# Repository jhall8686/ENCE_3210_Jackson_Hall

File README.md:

# ENCE_3210_Jackson_Hall
Microprocessor Systems Project Submissions

---

The primary project in this repository is the **ThermoPro Thermometer Probe**, a clone of an actual product implemented on a PCB shield. All of the PCB docs and firmware can be found here.

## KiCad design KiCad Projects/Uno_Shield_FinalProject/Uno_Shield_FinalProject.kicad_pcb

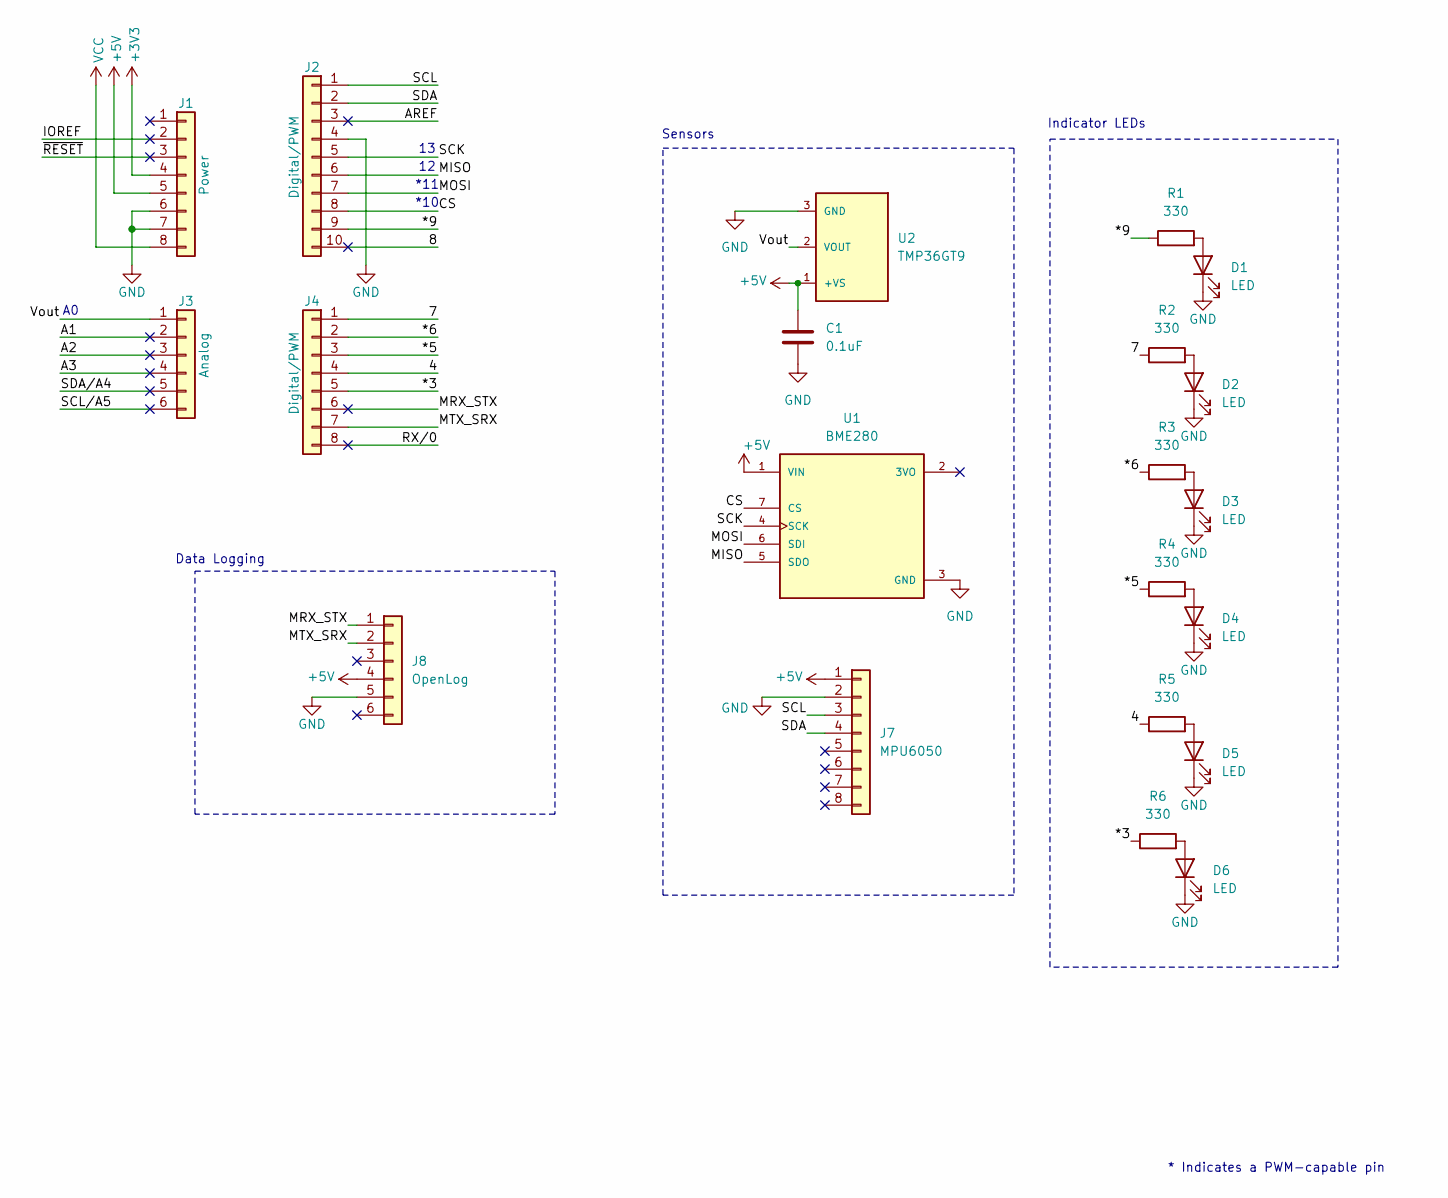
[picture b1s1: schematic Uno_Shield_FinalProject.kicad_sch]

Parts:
C1: 0.1uF; CP_Radial_D6.3mm_P2.50mm
D1, D2, D3, D4, D5, D6: LED; LED_D3.0mm
J1: Power; PinSocket_1x08_P2.54mm_Vertical
J2: Digital/PWM; PinSocket_1x10_P2.54mm_Vertical
J3: Analog; PinSocket_1x06_P2.54mm_Vertical
J4: Digital/PWM; PinSocket_1x08_P2.54mm_Vertical
J7: MPU6050; PinSocket_1x08_P2.54mm_Vertical
J8: OpenLog; MODULE_DEV-13712
R1, R2, R3, R4, R5, R6: 330; R_Axial_DIN0207_L6.3mm_D2.5mm_P10.16mm_Horizontal
U1: BME280; MODULE_2652; PARTREV N/A
U2: TMP36GT9; XDCR_TMP36GT9; PARTREV H

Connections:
+3V3: J1.4
+5V: C1.1, J1.5, J7.1, J8.4, U1.1 (VIN), U2.1 (+VS)
/4: J4.4, R5.1
/7: J4.1, R2.1
/8: J2.10
/*3: J4.5, R6.1
/*5: J4.3, R4.1
/*6: J4.2, R3.1
/*9: J2.9, R1.1
/A1: J3.2
/A2: J3.3
/A3: J3.4
/AREF: J2.3
/CS: J2.8, U1.7 (CS)
/IOREF: J1.2
/MISO: J2.6, U1.5 (SDO)
/MOSI: J2.7, U1.6 (SDI)
/MRX_STX: J4.6, J8.1
/MTX_SRX: J4.7, J8.2
/RX/0: J4.8
/SCK: J2.5, U1.4 (SCK)
/SCL: J2.1, J7.3
/SCL/A5: J3.6
/SDA: J2.2, J7.4
/SDA/A4: J3.5
/Vout: J3.1, U2.2 (VOUT)
/~RESET: J1.3
GND: C1.2, D1.1 (K), D2.1 (K), D3.1 (K), D4.1 (K), D5.1 (K), D6.1 (K), J1.6, J1.7, J2.4, J7.2, J8.5, U1.3 (GND), U2.3 (GND)
unnamed: D1.2 (A), R1.2
unnamed: D2.2 (A), R2.2
unnamed: D3.2 (A), R3.2
unnamed: D4.2 (A), R4.2
unnamed: D5.2 (A), R5.2
unnamed: D6.2 (A), R6.2
VCC: J1.8

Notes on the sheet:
*11
Data Logging
Indicator LEDs
Sensors
* Indicates a PWM-capable pin
*10

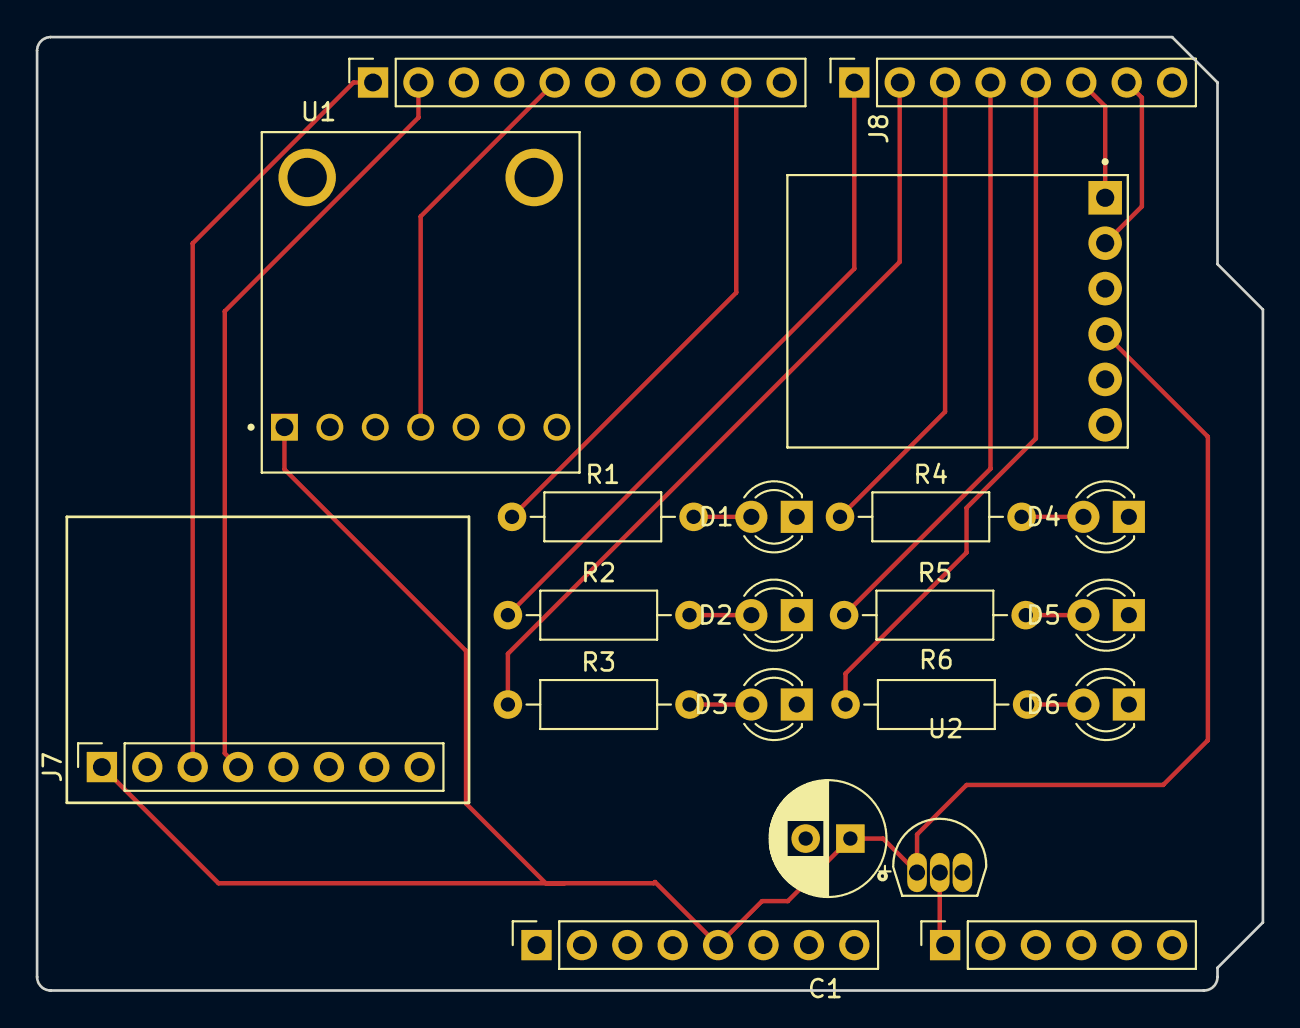
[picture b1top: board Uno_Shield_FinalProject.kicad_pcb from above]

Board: 2 copper layers, 68.6 x 53.3 mm, 21 parts (0 on the bottom side), 23 nets.

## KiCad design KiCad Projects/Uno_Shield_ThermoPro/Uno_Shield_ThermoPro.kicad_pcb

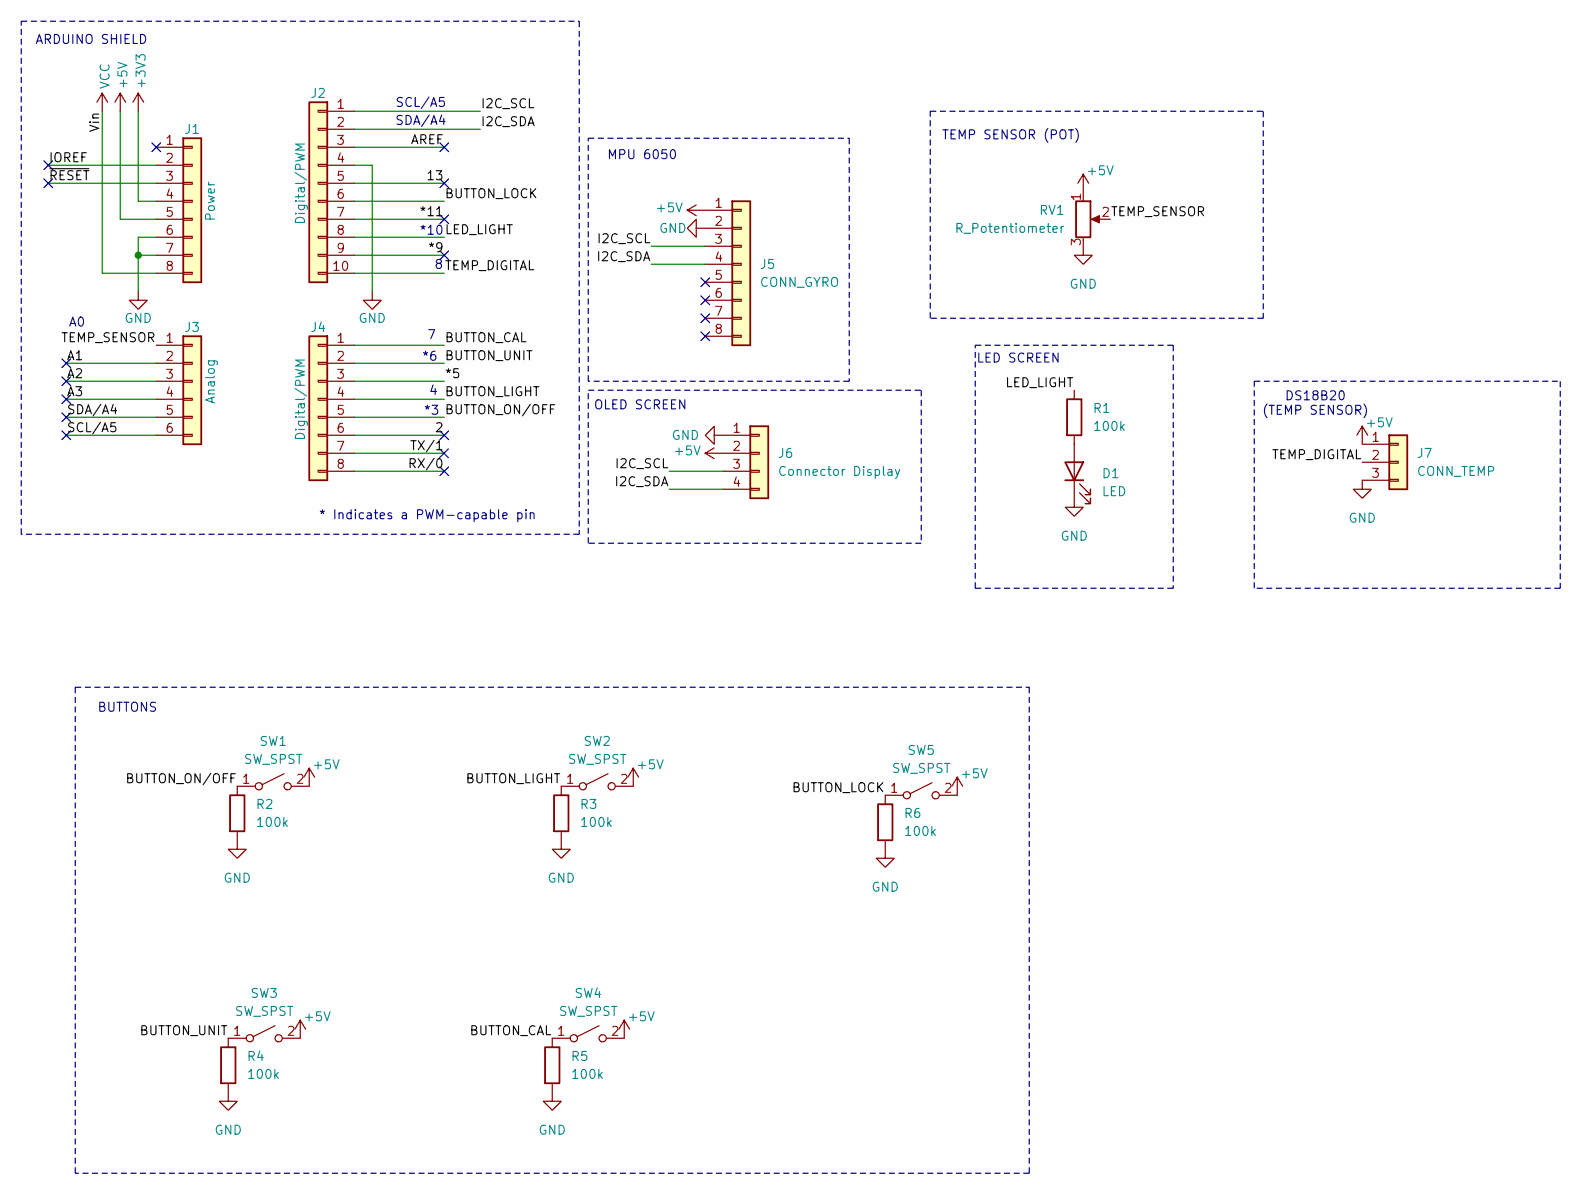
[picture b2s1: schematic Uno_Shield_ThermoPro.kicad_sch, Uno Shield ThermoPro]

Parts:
D1: LED; LED_D5.0mm
J1: Power; PinSocket_1x08_P2.54mm_Vertical
J2: Digital/PWM; PinSocket_1x10_P2.54mm_Vertical
J3: Analog; PinSocket_1x06_P2.54mm_Vertical
J4: Digital/PWM; PinSocket_1x08_P2.54mm_Vertical
J5: CONN_GYRO; PinSocket_1x08_P2.54mm_Vertical
J6: Connector Display; PinSocket_1x04_P2.54mm_Vertical
J7: CONN_TEMP; JST_XH_B3B-XH-A_1x03_P2.50mm_Vertical
R1, R2, R3, R4, R5, R6: 100k; R_Axial_DIN0207_L6.3mm_D2.5mm_P10.16mm_Horizontal
RV1: R_Potentiometer; Potentiometer_Bourns_3386P_Vertical
SW1, SW2, SW3, SW4, SW5: SW_SPST; SW_PUSH_6mm

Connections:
+3V3: J1.4
+5V: J1.5, J5.1, J6.2, J7.1, RV1.1, SW1.2 (B), SW2.2 (B), SW3.2 (B), SW4.2 (B), SW5.2 (B)
/2: J4.6
/13: J2.5
/*5: J4.3
/*9: J2.9
/*11: J2.7
/A1: J3.2
/A2: J3.3
/A3: J3.4
/AREF: J2.3
/BUTTON_CAL: J4.1, R5.1, SW4.1 (A)
/BUTTON_LIGHT: J4.4, R3.1, SW2.1 (A)
/BUTTON_LOCK: J2.6, R6.1, SW5.1 (A)
/BUTTON_ON/OFF: J4.5, R2.1, SW1.1 (A)
/BUTTON_UNIT: J4.2, R4.1, SW3.1 (A)
/I2C_SCL: J2.1, J5.3, J6.3
/I2C_SDA: J2.2, J5.4, J6.4
/IOREF: J1.2
/LED_LIGHT: J2.8, R1.1
/RX/0: J4.8
/SCL/A5: J3.6
/SDA/A4: J3.5
/TEMP_DIGITAL: J2.10, J7.2
/TEMP_SENSOR: J3.1, RV1.2
/TX/1: J4.7
/~RESET: J1.3
GND: D1.1 (K), J1.6, J1.7, J2.4, J5.2, J6.1, J7.3, R2.2, R3.2, R4.2, R5.2, R6.2, RV1.3
unnamed: D1.2 (A), R1.2
VCC: J1.8

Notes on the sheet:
MPU 6050
DS18B20 (TEMP SENSOR)
SDA/A4
*10
BUTTONS
ARDUINO SHIELD
LED SCREEN
* Indicates a PWM-capable pin
TEMP SENSOR (POT)
SCL/A5
OLED SCREEN

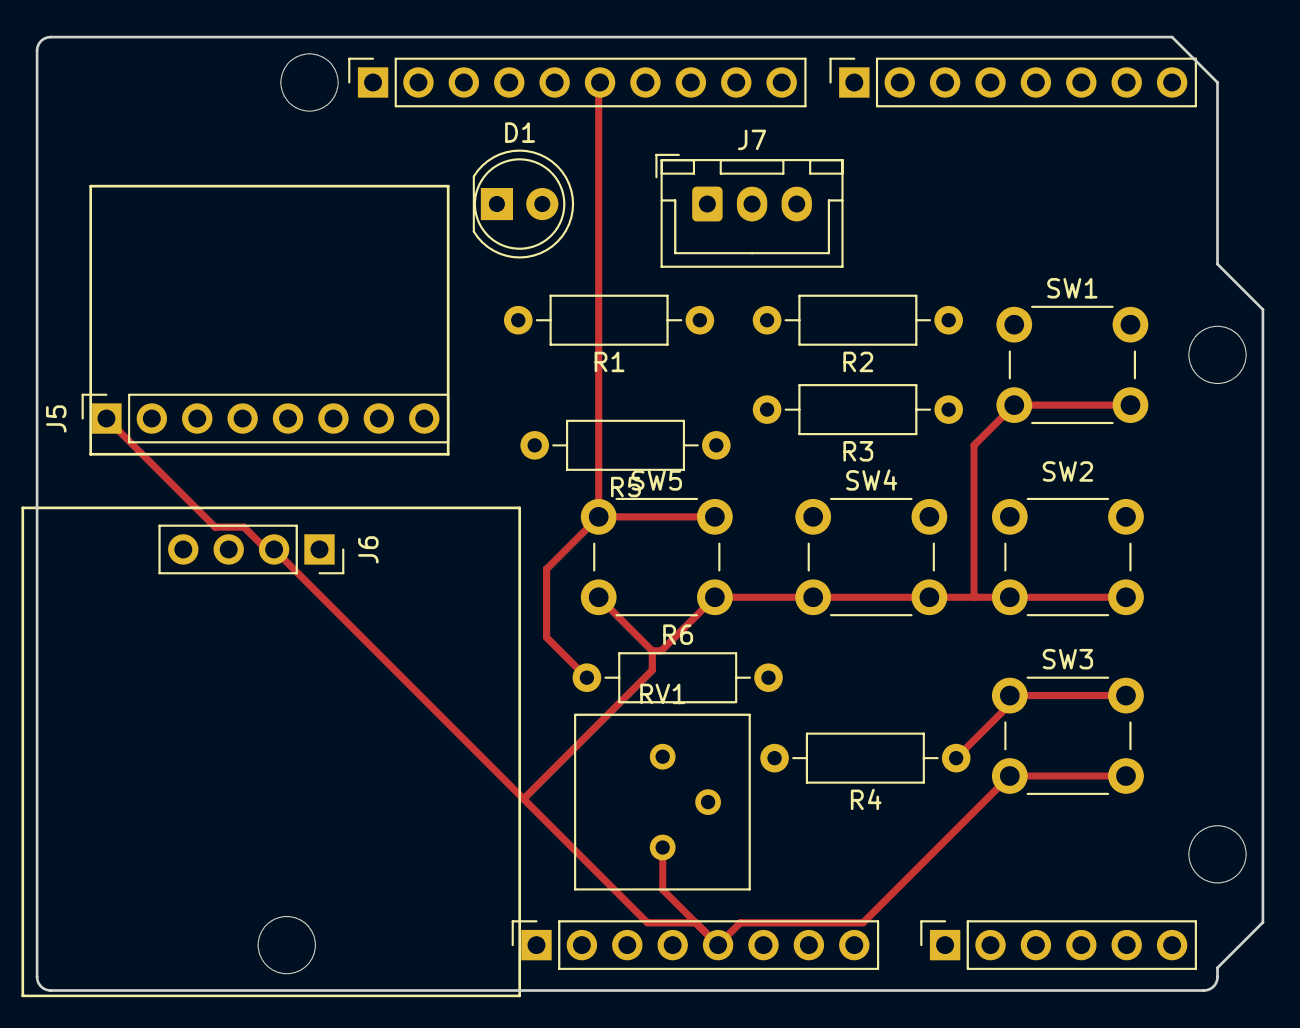
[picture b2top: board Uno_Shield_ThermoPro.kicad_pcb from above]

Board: 2 copper layers, 68.6 x 53.3 mm, 24 parts (0 on the bottom side), 13 nets.

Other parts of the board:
MH1, MH2, MH3, MH4: MountingHole_3.2mm

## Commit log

2025-01-10 Test
2025-01-13 Lab1 Push
2025-01-17 Lab 1 Code
2025-01-17 Problem 5 Code
2025-01-18 Delete Lab/Lab1Prob1 directory
    Do it
2025-01-18 Delete Lab/Lab1Prob2 directory
    do it
2025-01-18 Delete Lab/Lab1Prob3 directory
    Do it
2025-01-27 Forgot to commit on Friday, oops
2025-01-27 Lab 3
2025-02-03 KiCad Files
2025-02-04 ThermoPro Project v1
2025-02-24 ThermoPro Commit
2025-02-25 Final Firmware
2025-02-26 Diagrams and Library Updates
2025-02-26 Flowchart
2025-03-05 Lab 4 Commit, Sorry it's late!
2025-03-13 v1 Commit
2025-03-14 Final Project Commit
2025-03-14 PPT upload
2025-03-14 Final Project Presentation Upload
